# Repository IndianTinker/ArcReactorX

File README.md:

ArcReactorX
===========

An intelligent Arc Reactor that does morse code and tons of other cool animations
Uses commonly available parts and ICs sampled from TI.

The controller on-board is MSP430G2452 programmed using launchpad and coded using mspgcc

This project is released under CC BY-NC

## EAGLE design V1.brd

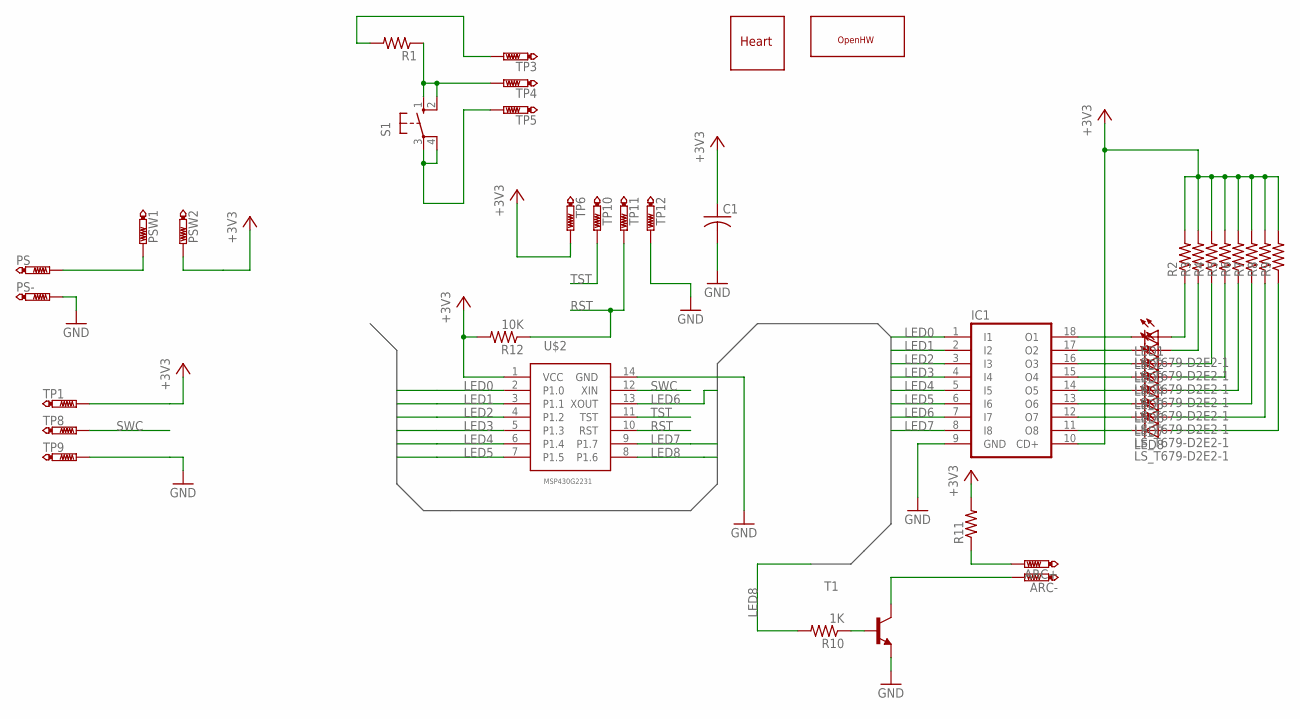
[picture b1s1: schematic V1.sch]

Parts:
ARC+: PTR1TP20SQ; TP20SQ
ARC-: PTR1TP20SQ; TP20SQ
C1: CAP0805; C0805
IC1: ULN2803A; DIL18
LED1, LED2, LED3, LED4, LED5, LED6, LED7, LED8: LS_T679-D2E2-1; PLCC2
PS: PTR1TP20SQ; TP20SQ
PS-: PTR1TP20SQ; TP20SQ
PSW1, PSW2: PTR1TP20SQ; TP20SQ
R1, R2, R3, R4, R5, R6, R9, R11: RESISTOR0805; R0805
R7: RESISTOR0207/10; 0207/10
R8: RESISTOR0207/7; 0207/7
R10: 1K; 0207/7
R12: 10K; R0805
S1: 40-XX; B3F-40XX
T1: MMBT3904LT1-NPN-SOT23-BEC; SOT23-BEC
TP1, TP3, TP4, TP5, TP6, TP8, TP9, TP10, TP11, TP12: PTR1TP20SQ; TP20SQ
U$1: HEARTTOPLAYER; HEART
U$2: MSP430G2231SOP; G2231TSSOP
U$3: OPENHWLOGO1; OPENHW

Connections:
+3V3: C1.1, IC1.10 (CD+), PSW2.TP, R2.2, R3.2, R4.2, R5.2, R6.2, R7.2, R8.2, R9.2, R11.2, R12.2, TP1.TP, TP6.TP, U$2.1 (VCC)
GND: C1.2, IC1.9 (GND), PS-.TP, T1.E, TP9.TP, TP12.TP, U$2.14 (GND)
LED0: IC1.1 (I1), U$2.2 (P1.0)
LED1: IC1.2 (I2), U$2.3 (P1.1)
LED2: IC1.3 (I3), U$2.4 (P1.2)
LED3: IC1.4 (I4), U$2.5 (P1.3)
LED4: IC1.5 (I5), U$2.6 (P1.4)
LED5: IC1.6 (I6), U$2.7 (P1.5)
LED6: IC1.7 (I7), U$2.13 (XOUT)
LED7: IC1.8 (I8), U$2.9 (P1.7)
LED8: R10.2, U$2.8 (P1.6)
unnamed: R10.1, T1.B
unnamed: PS.TP, PSW1.TP
unnamed: ARC-.TP, T1.C
unnamed: ARC+.TP, R11.1
unnamed: IC1.18 (O1), LED1.C
unnamed: IC1.17 (O2), LED2.C
unnamed: IC1.16 (O3), LED3.C
unnamed: IC1.15 (O4), LED4.C
unnamed: IC1.14 (O5), LED5.C
unnamed: IC1.13 (O6), LED6.C
unnamed: IC1.12 (O7), LED7.C
unnamed: IC1.11 (O8), LED8.C
unnamed: LED1.A, R2.1
unnamed: LED2.A, R3.1
unnamed: LED3.A, R4.1
unnamed: LED4.A, R5.1
unnamed: LED5.A, R6.1
unnamed: LED6.A, R7.1
unnamed: LED7.A, R8.1
unnamed: LED8.A, R9.1
unnamed: S1.3, S1.4 (P1), TP5.TP
unnamed: R1.1, S1.1 (S), S1.2 (S1), TP4.TP
unnamed: R1.2, TP3.TP
RST: R12.1, TP11.TP, U$2.10 (RST)
SWC: TP8.TP, U$2.12 (XIN)
TST: TP10.TP, U$2.11 (TST)

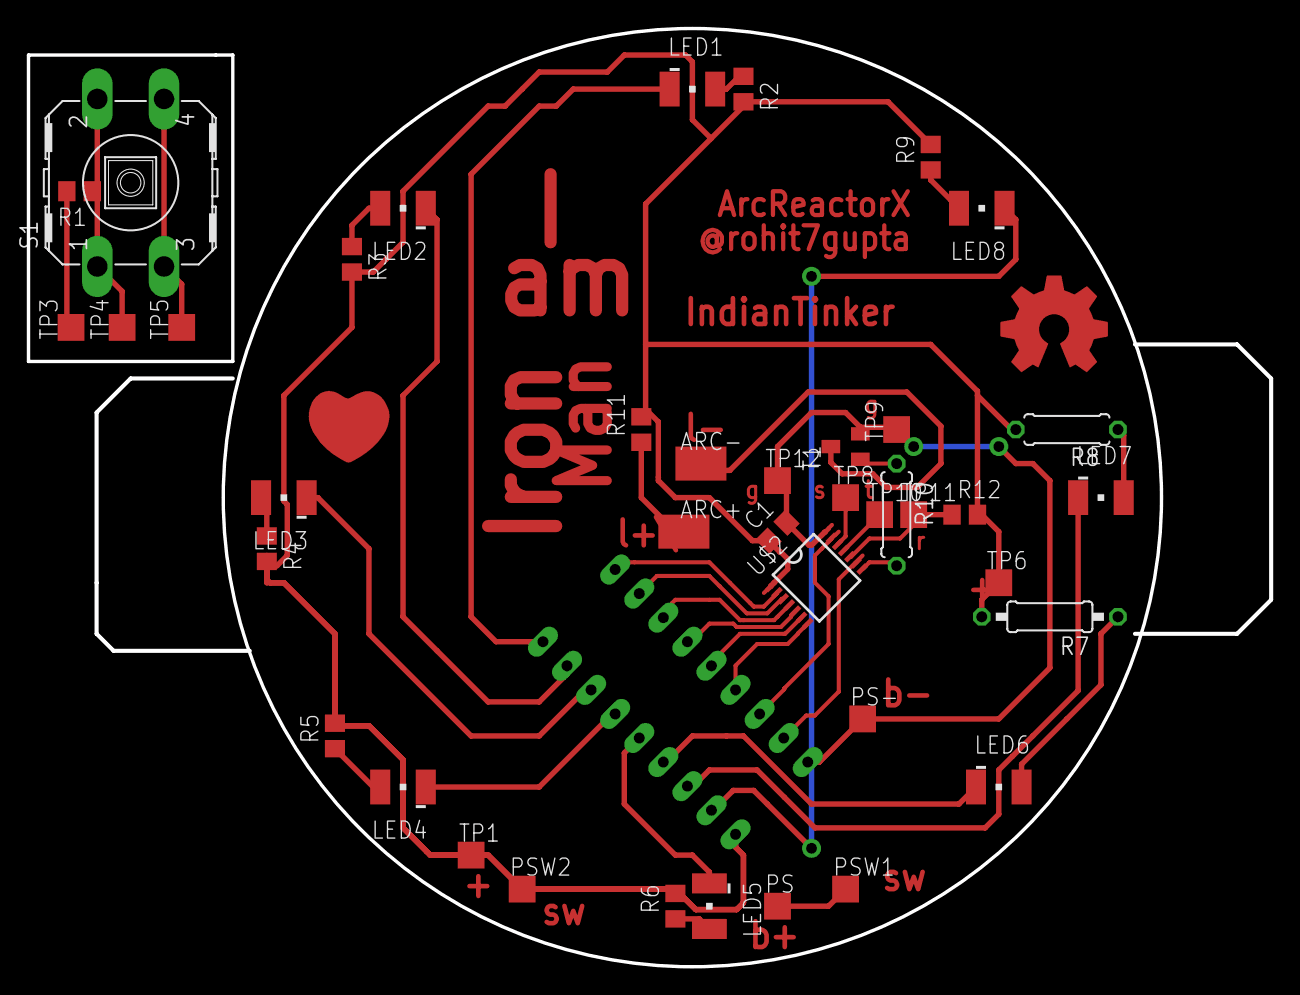
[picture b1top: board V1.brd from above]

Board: 2 copper layers, 92.7 x 69.9 mm, 43 parts (1 on the bottom side), 37 nets.

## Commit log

2014-02-08 Files Added
2014-04-14 Experimental Code added
2014-04-16 new version added with variuos modes! I am having slight issues with debounce. But this is what i am taking to ComicCon
